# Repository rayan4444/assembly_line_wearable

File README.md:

# Crimson Dynamic

Hardware files and code for Crimson Dynamic (HAX Shenzhen 2019) sensor system prototyping

## Objective
Design a sensor system that adds value to the exoskeleton, specifically for use in an overhead assembly line in car factories. Potential insights the sensor system could provide:
* Task compliance: ensure a worker did not forget a bolt/nut on a car
* long term vibration exposure
* long term arm fatigue
* long term noise exposure
 * etc.

## REV 1
Sensor breakout to count the number of overhead drilling actions accomplished. Looked into doing an FFT analysis on IMU data and microphone data. Decided to settle on matching IMU data peaks to microphone data peaks. The same two sensors could be use to quantify the long term exposure to vibration, noise and fatigue.

## REV2
Pi HAT with sensors and UI to count the number of overhead drilling actions accomplished. A more efficient rendition of REV1 that is usable for demonstration.
> Note: Data is post processed and results are not given in real time

## REV3
NRF52 based sensor node with only IMU to monitor limb motion and vibration

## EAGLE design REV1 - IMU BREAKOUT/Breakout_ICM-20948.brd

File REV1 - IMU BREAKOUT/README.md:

Crimson Dynamics REV1

## Decription
Tries to detect drilling acitons by matching accelerometer peaks to microphone peaks. 
- Attempted doing it purely by placing the IMU on the hand holding the drill and running FFT but as the body acted as a low pass filter and filetered out higher frequencies that could have had information to characterise drilling vibrations. 
- Decided to addd a microphone to provide a second input. 
- In the final iteration of REV1, a simple peak finding algorithm from signal.scipy library is used to identify peaks in accelration and microphone recording. If the peaks happen within a second from each other they are assumed to belong to the same drilling action. Assuming the worker only does drilling tasks, this can be used to count the number of tasks. 

#### Notes:
- detailed assumptions in code
- sigle movements (vs vibrations) are not counted as drilling motion reducing false positives. 
- the code is in different scripts and run very slowly. 

## Hardware files 
ICM20948 breakout board slightly modified from the [Sparkfun one](https://www.sparkfun.com/products/15335)
## Python scripts 
#### Crimson_data_log.py
Records 10s of IMU and Microphone data, saves it in files "sensor_log.csv" and "output.wav" respectively. Later splits sensor log in "ax.csv", "ay.csv" and "az.csv" for further analysis. 

#### Crimson_action_count.py
- Opens data files and runs peak finding algorithm 
- Plots peaks found 
- For each of ax, ay, az and mic data, groups peaks that are within 0.5 seconds of each other as belonging to one "action" 
- To reduce the occurrance of false positives, only considers "actions" with peaks in at least two of the 3 accelerometer axes. 
- Only Counts "actions" with peaks in both microphone and accelerometer data (peak cluster averages within 1s of each other) 
- Prints total numberof valid "actions"

## OLD CODE
All the other python scripts used to test various things, such as IMU and microphone recording, data hadnling and plotting, FFT analysis etc. 

## TEST DATA
Data recorded with the prototype and used to tweak the peak finidng algorithm. TEST 5 is the best. 
In this version:
- 1 x ICM20948 9-Dof IMU (Eagle files for the breakout board are in this folder) 
- 1 x SPH0645LM4H MEMS Microphone breakout (from taobao)
- 1x Raspberry Pi (Raspberry Pi Zero W v1.1 used in my tests)

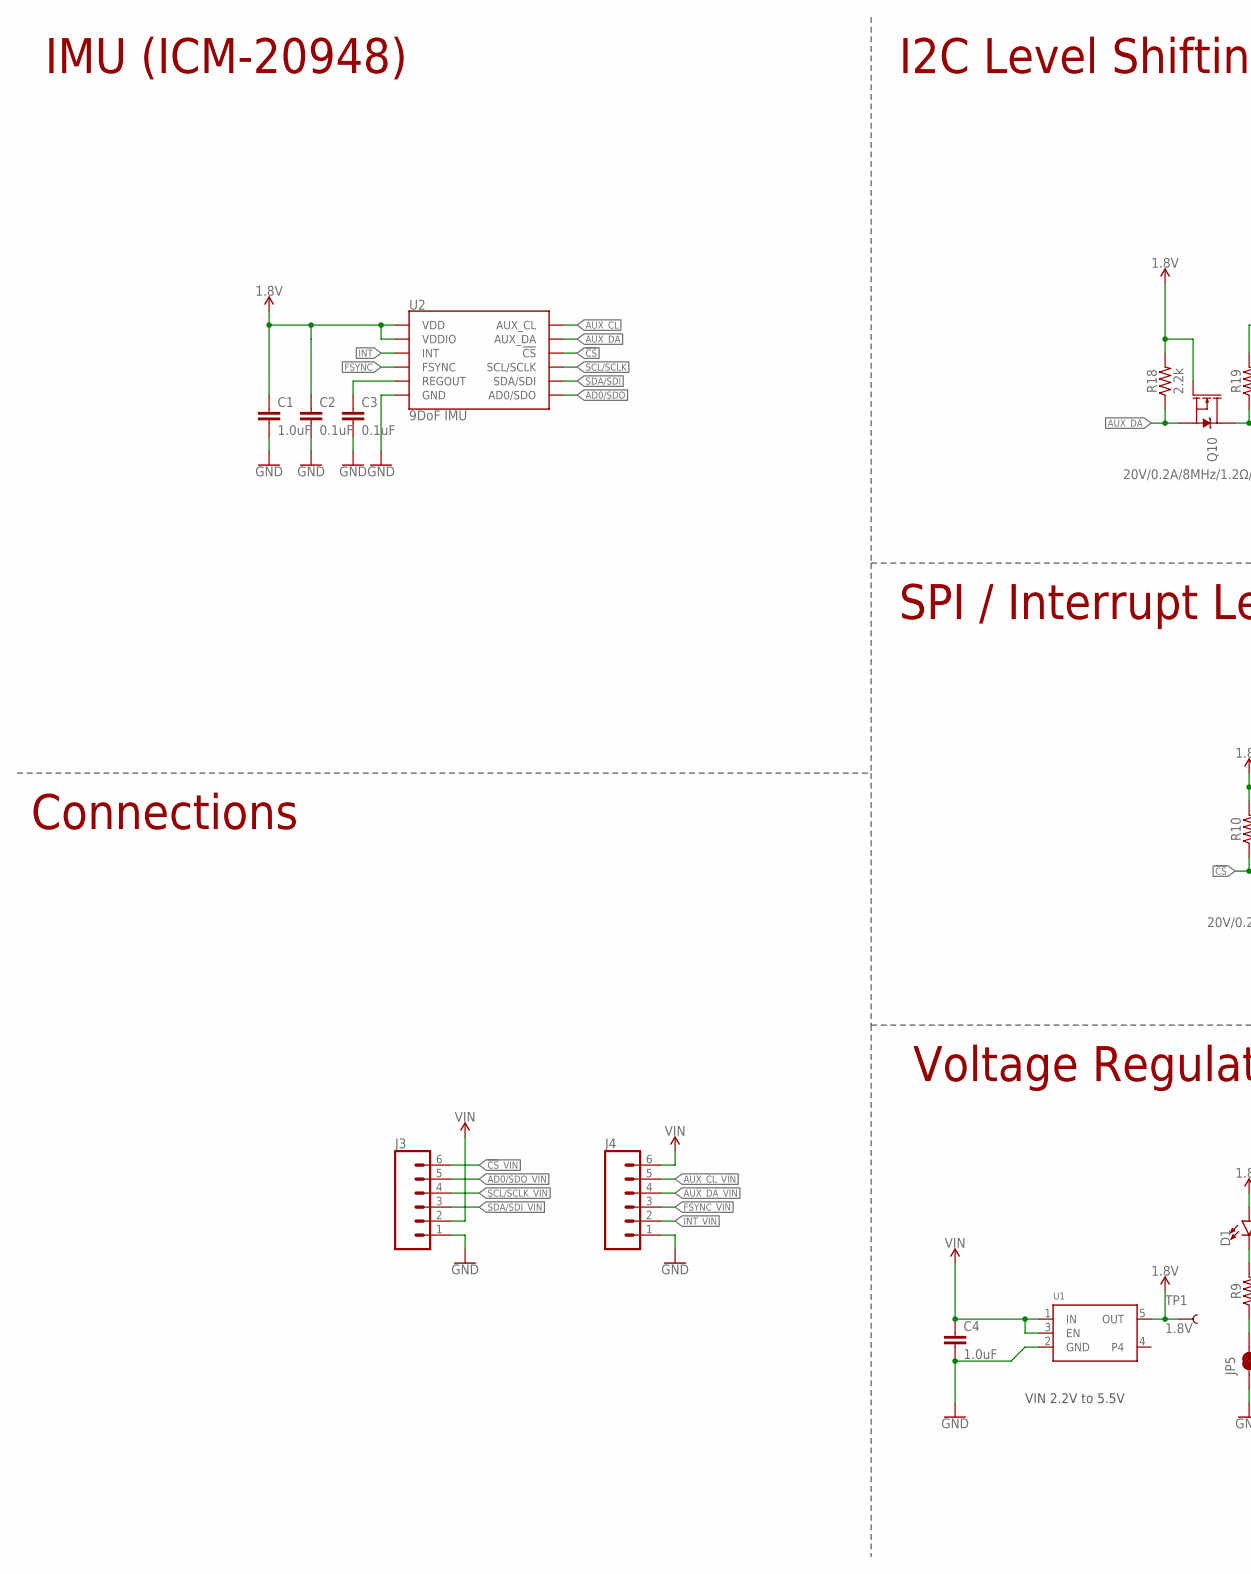
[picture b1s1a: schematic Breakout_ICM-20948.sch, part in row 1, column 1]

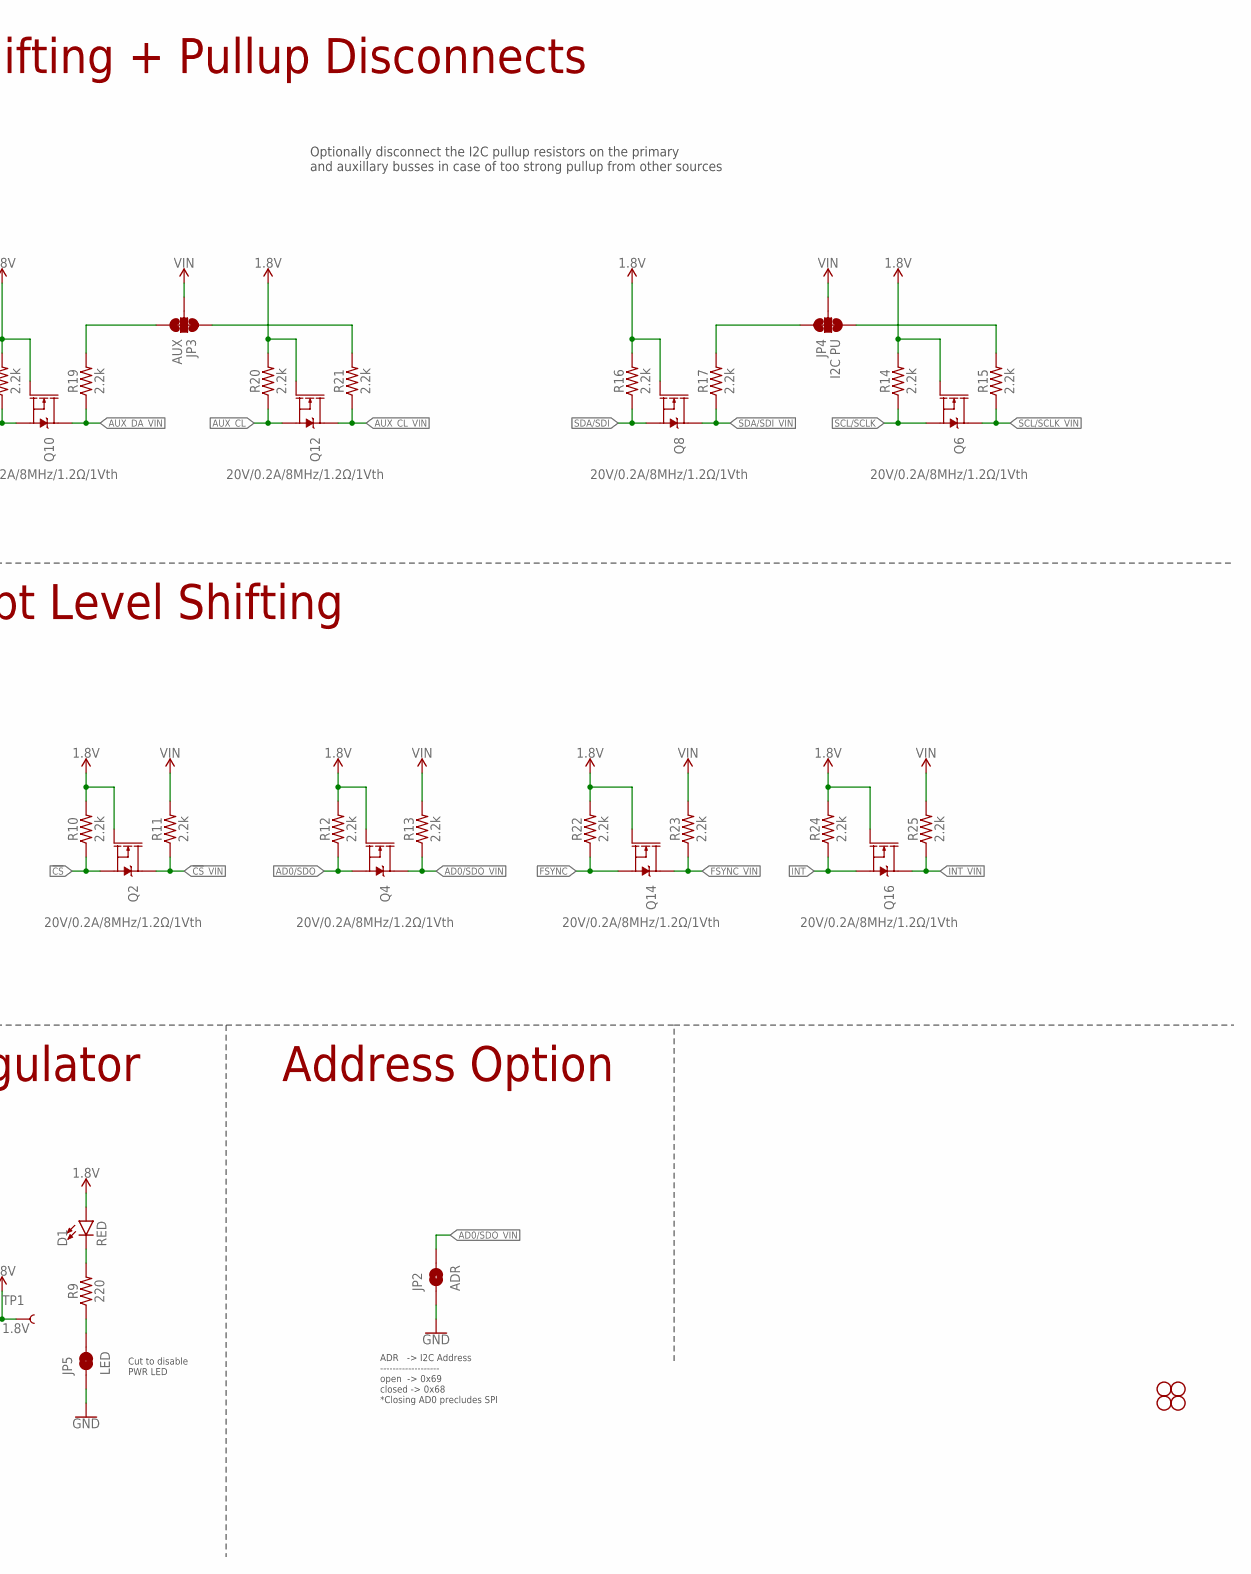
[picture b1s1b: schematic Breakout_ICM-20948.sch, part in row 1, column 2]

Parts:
C1, C4: 1.0uF; 0603
C2, C3: 0.1uF; 0603
D1: RED; LED-0603
H1, H2, H3, H4: STAND-OFF
J3, J4: CONN_06NO_SILK_NO_POP; 1X06_NO_SILK
JP2: ADR; SMT-JUMPER_2_NO_SILK
JP3: AUX; SMT-JUMPER_3_2-NC_TRACE_SILK
JP4: I2C PU; SMT-JUMPER_3_2-NC_TRACE_SILK
JP5: LED; SMT-JUMPER_2_NC_TRACE_SILK
Q2, Q4, Q6, Q8, Q10, Q12, Q14, Q16: 20V/0.2A/8MHz/1.2Ω/1Vth; SOT-416FL
R9: 220; 0603
R10, R11, R12, R13, R14, R15, R16, R17, R18, R19, R20, R21, R22, R23, R24, R25: 2.2k; 0402-TIGHT
TP1: 1.8V; PAD.03X.03
U1: MICROBUILDER_VREG_SOT23-5; MICROBUILDER_SOT23-5
U2: 9DoF IMU; QFN24-3X3

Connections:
1.8V: C1.1, C2.1, D1.A, Q2.1 (G), Q4.1 (G), Q6.1 (G), Q8.1 (G), Q10.1 (G), Q12.1 (G), Q14.1 (G), Q16.1 (G), R10.2, R12.2, R14.2, R16.2, R18.2, R20.2, R22.2, R24.2, TP1.P$1, U1.5 (OUT), U2.8 (VDDIO), U2.13 (VDD)
!CS: Q2.2 (S), R10.1, U2.22 (!CS)
!CS!_VIN: J3.6, Q2.3 (D), R11.1
AD0/SDO: Q4.2 (S), R12.1, U2.9 (AD0/SDO)
AD0/SDO_VIN: J3.5, JP2.2, Q4.3 (D), R13.1
AUX_CL: Q12.2 (S), R20.1, U2.7 (AUX_CL)
AUX_CL_VIN: J4.5, Q12.3 (D), R21.1
AUX_DA: Q10.2 (S), R18.1, U2.21 (AUX_DA)
AUX_DA_VIN: J4.4, Q10.3 (D), R19.1
FSYNC: Q14.2 (S), R22.1, U2.11 (FSYNC)
FSYNC_VIN: J4.3, Q14.3 (D), R23.1
GND: C1.2, C2.2, C3.2, C4.2, J3.1, J4.1, JP2.1, JP5.1, U1.2 (GND), U2.18 (GND), U2.20 (GND)
INT: Q16.2 (S), R24.1, U2.12 (INT)
INT_VIN: J4.2, Q16.3 (D), R25.1
unnamed: C3.1, U2.10 (REGOUT)
unnamed: JP4.3, R15.2
unnamed: JP4.1, R17.2
unnamed: JP3.1, R21.2
unnamed: JP3.3, R19.2
unnamed: D1.C, R9.2
unnamed: JP5.2, R9.1
SCL/SCLK: Q6.2 (S), R14.1, U2.23 (SCL/SCLK)
SCL/SCLK_VIN: J3.4, Q6.3 (D), R15.1
SDA/SDI: Q8.2 (S), R16.1, U2.24 (SDA/SDI)
SDA/SDI_VIN: J3.3, Q8.3 (D), R17.1
VIN: C4.1, J3.2, J4.6, JP3.2, JP4.2, R11.2, R13.2, R23.2, R25.2, U1.1 (IN), U1.3 (EN)

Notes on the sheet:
VIN 2.2V to 5.5V
IMU (ICM-20948)
I2C Level Shifting + Pullup Disconnects
Connections
Voltage Regulator
SPI / Interrupt Level Shifting
ADR -> I2C Address ------------------- open -> 0x69 closed -> 0x68 *Closing AD0 precludes SPI
Optionally disconnect the I2C pullup resistors on the primary and auxillary busses in case of too strong pullup from other sources
Cut to disable PWR LED
Address Option

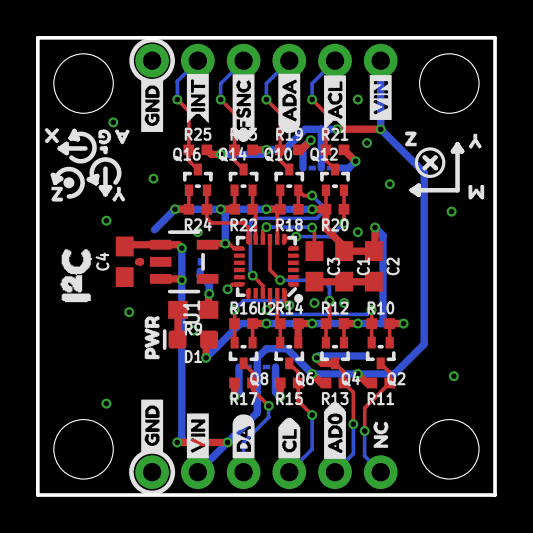
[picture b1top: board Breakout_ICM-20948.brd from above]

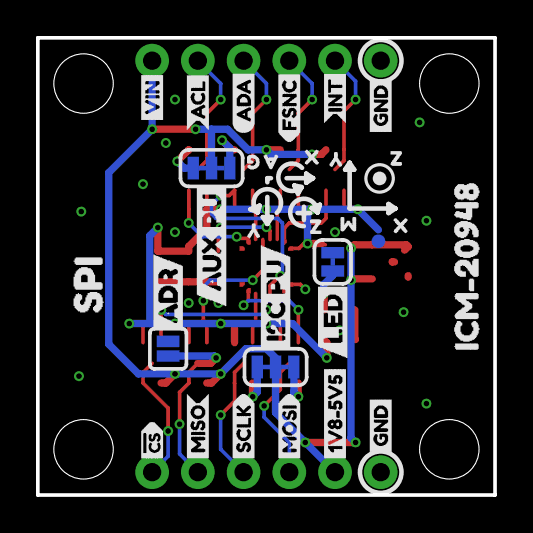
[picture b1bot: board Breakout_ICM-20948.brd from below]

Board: 2 copper layers, 25.4 x 25.4 mm, 92 parts (32 on the bottom side), 26 nets.

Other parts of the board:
U$1, U$2, U$22, U$24: GND4
U$3: PWR0
U$4, U$21: INT3
U$5, U$20: FSNC2
U$6, U$19: ACL1
U$7, U$18: ADA0
U$8: MISO13
U$9: MOSI14
U$10: SCLK15
U$11: #CS16
U$12: 1V8#5V57
U$13, U$30, U$44: VIN5
U$14: NC17
U$15: CL4
U$16: DA2
U$17: AD012
U$23: ADR2
U$25: I2C_PU21
U$26: SPI19
U$27: AUX_PU24
U$29: LED23
U$31: ICM#2094820
U$34, U$50, U$57: X0
U$35, U$41, U$51, U$58: Y1
U$36, U$42, U$52, U$59: Z2
U$37, U$60: G5
U$38, U$61: A4
U$39, U$49: M3
U$45: I#C1

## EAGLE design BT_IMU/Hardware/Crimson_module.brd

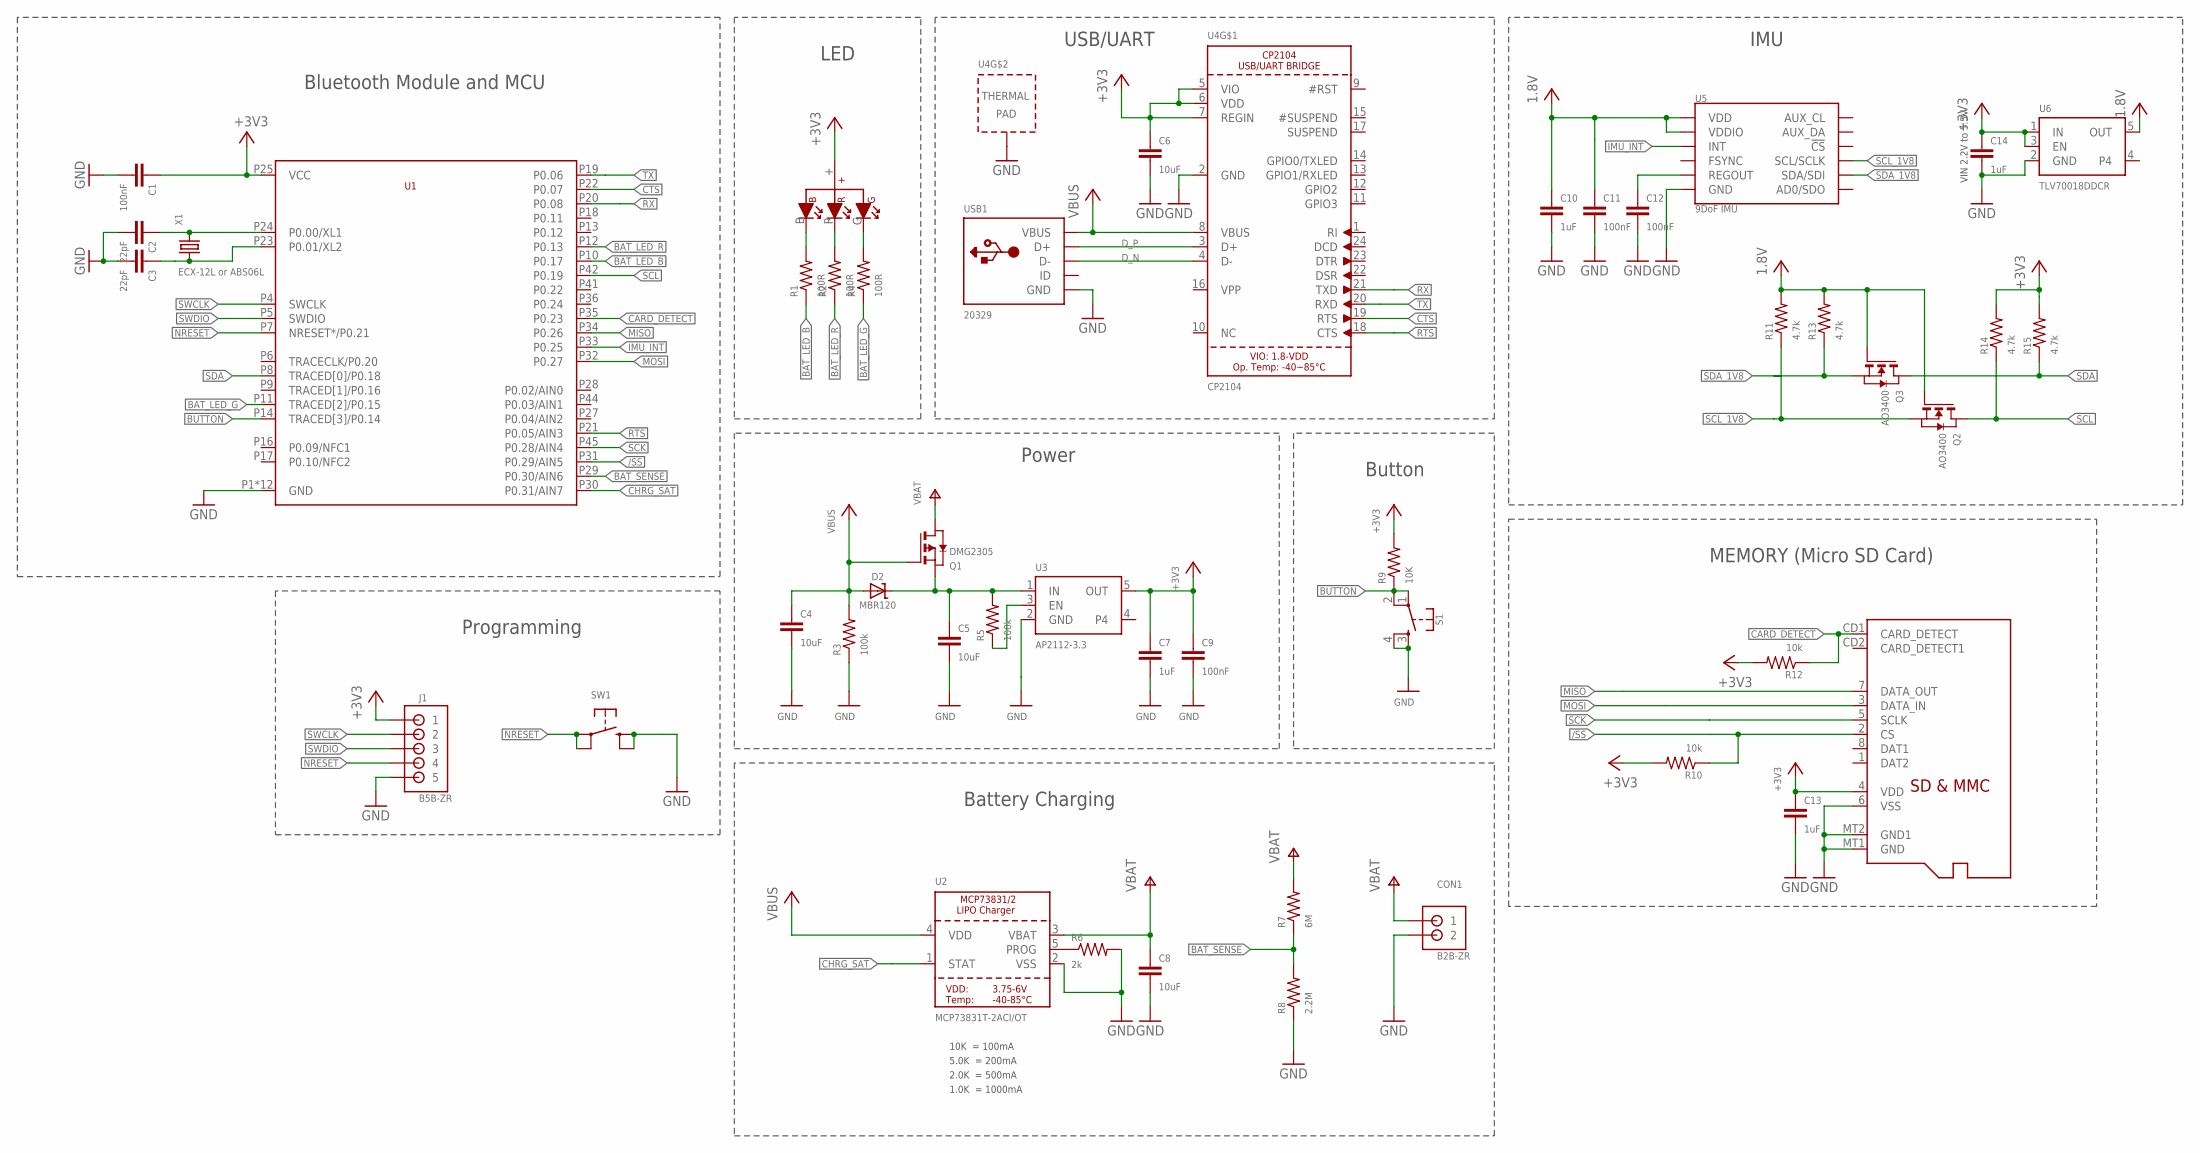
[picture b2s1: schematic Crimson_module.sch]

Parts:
C1, C9, C11, C12: 100nF; C0402
C2, C3: 22pF; C0402
C4, C5, C6, C8: 10uF; C0402
C7, C10, C13, C14: 1uF; C0402
CON1: B2B-ZR
D1: B2020RGBA
D2: MBR120; SOD-123
J1: B5B-ZR
Q1: DMG2305; SOT-23
Q2, Q3: AO3400; SOT-23
R1, R2, R4: 100R; R0402
R3, R5: 100k; R0402
R6: 2k; R0402
R7: 6M; R0402
R8: 2.2M; R0402
R9: 10K; R0402
R10, R12: 10k; R0402
R11, R13, R14, R15: 4.7k; R0402
S1: MOMENTARY-SWITCH-SPST-2-SMD-5.2MM; TACTILE_SWITCH_SMD_5.2MM
SD1: MICROSD
SW1: MICROBUILDER_SWITCH_TACT_SMT4.6X2.8; MICROBUILDER_BTN_KMR2_4.6X2.8
U1: BMD-350
U2: MCP73831T-2ACI/OT; SOT23-5
U3: AP2112-3.3; SOT23-5
U4: CP2104; QFN24_4MM_SMSC
U5: 9DoF IMU; QFN24-3X3
U6: TLV70018DDCR; MICROBUILDER_SOT23-5
USB1: 20329; 4UCONN_20329_V2
X1: ECX-12L or ABS06L; 2.0X1.2

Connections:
+3V3: C1.1, C6.1, C7.1, C9.1, C13.1, C14.1, D1.+, J1.1, R9.2, R10.2, R12.2, R14.2, R15.2, SD1.4 (VDD), U1.P25 (VCC), U3.5 (OUT), U4.5 (VIO), U4.6 (VDD), U4.7 (REGIN), U6.1 (IN), U6.3 (EN)
+5V: C4.1, D2.A, Q1.G, R3.2, U2.4 (VDD), U4.8 (VBUS), USB1.VBUS
/SS: R10.1, SD1.2 (CS), U1.P31 (P0.29/AIN5)
BAT_LED_B: R1.1, U1.P10 (P0.17)
BAT_LED_G: R4.1, U1.P11 (TRACED[2]/P0.15)
BAT_LED_R: R2.1, U1.P12 (P0.13)
BAT_SENSE: R7.1, R8.2, U1.P29 (P0.30/AIN6)
BUTTON: R9.1, S1.1, S1.2, U1.P14 (TRACED[3]/P0.14)
CARD_DETECT: R12.1, SD1.CD1 (CARD_DETECT), U1.P35 (P0.23)
CHRG_SAT: U1.P30 (P0.31/AIN7), U2.1 (STAT)
CTS: U1.P22 (P0.07), U4.19 (RTS)
D_N: U4.4 (D-), USB1.D-
D_P: U4.3 (D+), USB1.D+
EN: R5.1, U3.3 (EN)
GND: C1.2, C2.2, C3.2, C4.2, C5.2, C6.2, C7.2, C8.2, C9.2, C10.2, C11.2, C12.2, C13.2, C14.2, CON1.2, J1.5, R3.1, R6.2, R8.1, S1.3, S1.4, SD1.6 (VSS), SD1.MT1 (GND), SD1.MT2 (GND1), SW1.B (S), SW1.B' (S1), U1.P1 (GND), U1.P2 (GND), U1.P3 (GND), U1.P15 (GND), U1.P26 (GND), U1.P37 (GND), U1.P38 (GND), U1.P39 (GND), U1.P40 (GND), U1.P43 (GND), U1.P46 (GND), U1.P47 (GND), U2.2 (VSS), U3.2 (GND), U4.2 (GND), U4.THERM (TP), U5.18 (GND), U5.20 (GND), U6.2 (GND), USB1.BASE@1 (GND), USB1.BASE@2 (GND), USB1.GND, USB1.SPRT@1 (GND), USB1.SPRT@2 (GND), USB1.SPRT@3 (GND), USB1.SPRT@4 (GND)
IMU_INT: U1.P33 (P0.25), U5.12 (INT)
MISO: SD1.7 (DATA_OUT), U1.P34 (P0.26)
MOSI: SD1.3 (DATA_IN), U1.P32 (P0.27)
unnamed: R6.1, U2.5 (PROG)
unnamed: C12.1, U5.10 (REGOUT)
unnamed: C3.1, U1.P23 (P0.01/XL2), X1.1
unnamed: D1.B, R1.2
unnamed: D1.R, R2.2
unnamed: D1.G, R4.2
unnamed: C2.1, U1.P24 (P0.00/XL1), X1.2
unnamed: C5.1, D2.C, Q1.S, R5.2, U3.1 (IN)
NRESET: J1.4, SW1.A, SW1.A' (P1), U1.P7 (NRESET*/P0.21)
RTS: U1.P21 (P0.05/AIN3), U4.18 (CTS)
RX: U1.P20 (P0.08), U4.21 (TXD)
SCK: SD1.5 (SCLK), U1.P45 (P0.28/AIN4)
SCL: Q2.D, R14.1, U1.P42 (P0.19)
SCL_1V8: Q2.S, R11.1, U5.23 (SCL/SCLK)
SDA: Q3.D, R15.1, U1.P8 (TRACED[0]/P0.18)
SDA_1V8: Q3.S, R13.1, U5.24 (SDA/SDI)
SWCLK: J1.2, U1.P4 (SWCLK)
SWDIO: J1.3, U1.P5 (SWDIO)
TX: U1.P19 (P0.06), U4.20 (RXD)
V+: C8.1, CON1.1, Q1.D, R7.2, U2.3 (VBAT)
VCC: C10.1, C11.1, Q2.G, Q3.G, R11.2, R13.2, U5.8 (VDDIO), U5.13 (VDD), U6.5 (OUT)

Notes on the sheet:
10K = 100mA
5.0K = 200mA
2.0K = 500mA
1.0K = 1000mA
Battery Charging
Bluetooth Module and MCU
LED
USB/UART
Power
Button
MEMORY (Micro SD Card)
IMU
VIN 2.2V to 5.5V
Programming

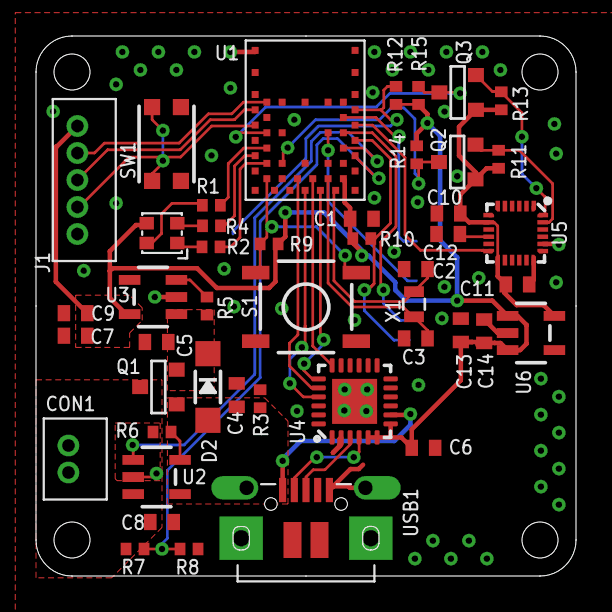
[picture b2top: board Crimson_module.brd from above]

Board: 2 copper layers, 30.0 x 30.0 mm, 47 parts (1 on the bottom side), 39 nets.

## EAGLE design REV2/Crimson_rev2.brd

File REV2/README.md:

Crimson Dynamics REV2

## Description
Pi HAT with sensors and UI to count the number of overhead drilling actions accomlished:
- 1 x ICM20948 9-Dof IMU 
- 1 x SPH0645LM4H MEMS Microphone
- 3 x pushbuttons
- 2 x LEDs
- 1 x 128x32 I2C OLED Display 
- 1 x Raspberry Pi Zero W v1.1

#### Python scripts
Crimson_button.py runs at boot and imports functions from Crimson_data_log.py and Crimson_action_count.py

#### Usage:
- Boot up the Rasberry Pi and wait for the OLED display to refresh. This might take up to 3-4 min.  
- Pressing "start" button records 40s of data from the microphone and the IMU (x,y,z acceleration to be specific). 
- Green LED lights up and stays on after the recording is done if everything went well 
- Pressing "stop" button analyses results, using the latest action counting technique from rev1.
> By default plotting is not enabled because it slows everything down and requires a way to close the plot window to proceed. but in case it is needed, plt.show() can be uncommented from Crimson_action_count.py
- Orange LED lights up and stays on after processing is done if everything went well. The final count will show on the display for a couple seconds. 
- Pressing "BTN" button deletes all data records. If you want to keep the recorded data, ssh into the Rpi and copy it to another directory before deleting it. 
> If you don't delete the data, the next recording will just be appended to the current file and give false action count results. 

#### Notes: 
- Display breakout on the PCB doesn't match the module we purchsed so some reworking had to be done to be able to wire it properly 
- A single python script that can be run from boot. It imports functions from two other python files. These functions are very similar to the REV1 code, a little has been done to optimise it. 
- To view code outputs you can hook up a display to the pi or ssh into it (or use VNC). You can also uncomment print statements in the code to track the action countinfg process. 
- [Tutorial to change microphone sensitivity](https://learn.adafruit.com/adafruit-i2s-mems-microphone-breakout/raspberry-pi-wiring-and-test)

## Hardware files
Eagle files and gerber files for the Pi HAT

## Other files
* Notes from meeting with Bunnie on 24.09.2019, discussing how to go about improving the current demo and going about the next version

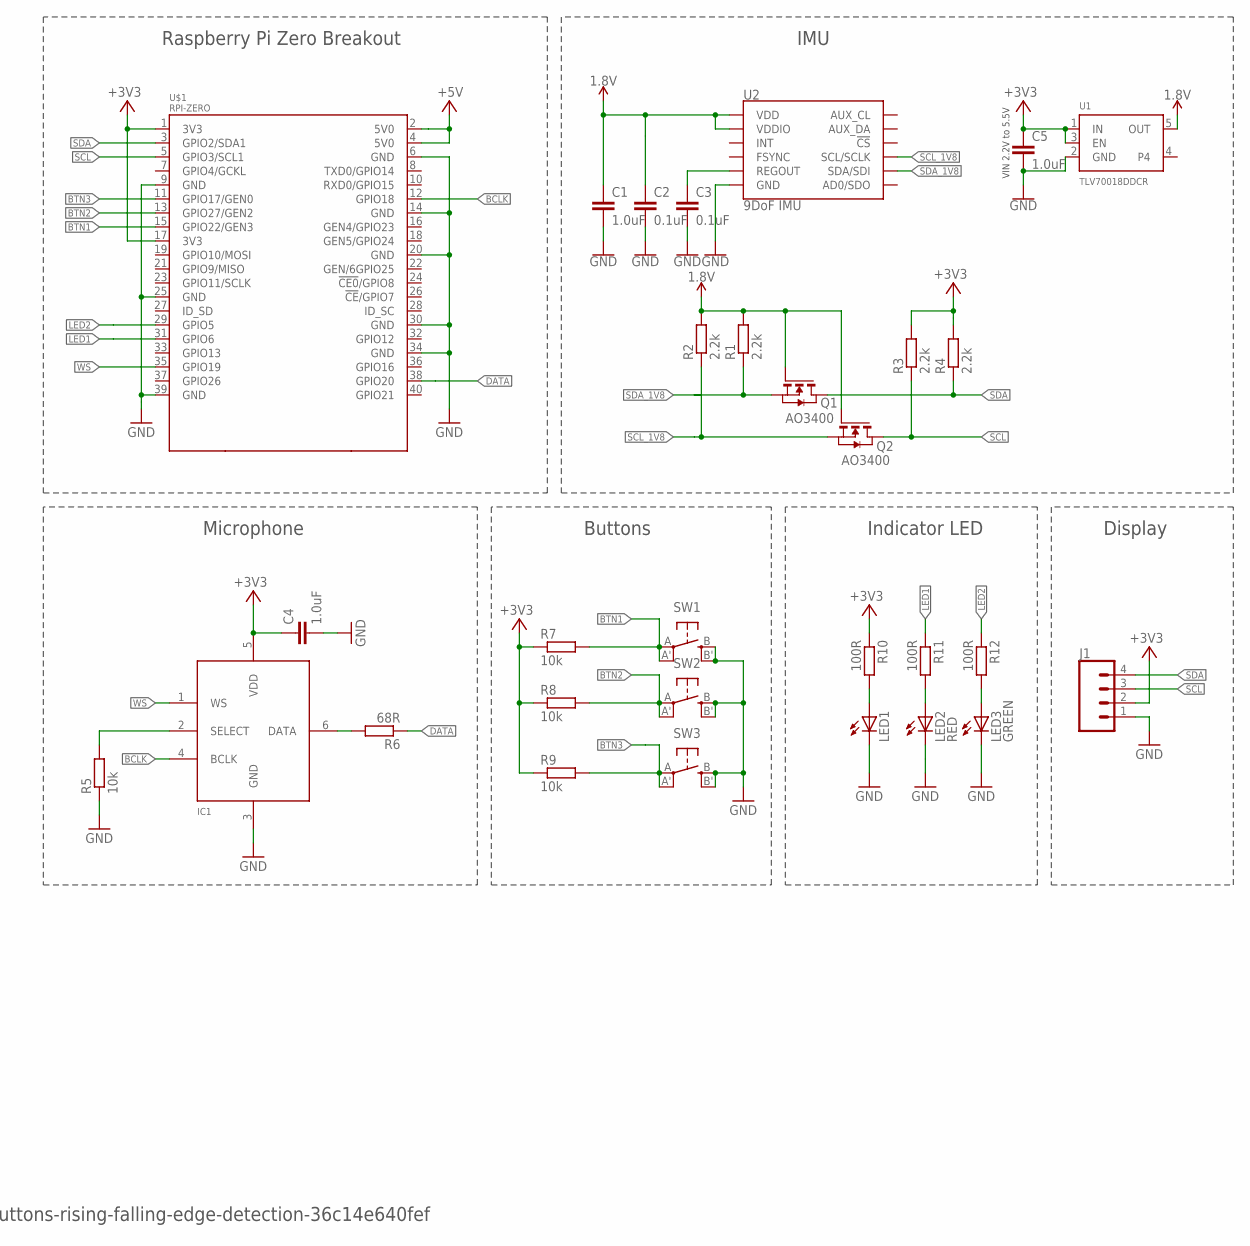
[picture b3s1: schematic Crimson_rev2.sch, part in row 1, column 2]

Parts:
C1, C4, C5: 1.0uF; 0402
C2, C3: 0.1uF; 0402
IC1: MIC_I2S_SPH0645; SPH0645LM4H
J1: CONN_04; 1X04
LED1: LEDCHIPLED_0603; CHIPLED_0603
LED2: RED; CHIPLED_0603
LED3: GREEN; CHIPLED_0603
Q1, Q2: AO3400; SOT-23
R1, R2, R3, R4: 2.2k; R0402
R5, R7, R8, R9: 10k; R0402
R6: 68R; R0402
R10, R11, R12: 100R; R0402
SW1, SW2, SW3: SPST_TACT-EVQQ2; EVQ-Q2
U1: TLV70018DDCR; MICROBUILDER_SOT23-5
U2: 9DoF IMU; QFN24-3X3
U$1: RPI-ZERO; RASPBERRYPI_BASTELSTUBE_V13_RASPI_BOARD_B+_FULL

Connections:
1.8V: C1.1, C2.1, Q1.G, Q2.G, R1.2, R2.2, U1.5 (OUT), U2.8 (VDDIO), U2.13 (VDD)
+3V3: C4.1, C5.1, IC1.5 (VDD), J1.2, R3.2, R4.2, R7.2, R8.2, R9.2, R10.1, U1.1 (IN), U1.3 (EN), U$1.1 (3V3), U$1.17 (3V3)
+5V: U$1.2 (5V0), U$1.4 (5V0)
BCLK: IC1.4 (BCLK), U$1.12 (GPIO18)
BTN1: R7.1, SW1.A, SW1.A' (P1), U$1.15 (GPIO22/GEN3)
BTN2: R8.1, SW2.A, SW2.A' (P1), U$1.13 (GPIO27/GEN2)
BTN3: R9.1, SW3.A, SW3.A' (P1), U$1.11 (GPIO17/GEN0)
DATA: R6.1, U$1.38 (GPIO20)
GND: C1.2, C2.2, C3.2, C4.2, C5.2, IC1.3 (GND), J1.1, LED1.C, LED2.C, LED3.C, R5.1, SW1.B (S), SW1.B' (S1), SW2.B (S), SW2.B' (S1), SW3.B (S), SW3.B' (S1), U1.2 (GND), U2.18 (GND), U2.20 (GND), U$1.6 (GND), U$1.9 (GND), U$1.14 (GND), U$1.20 (GND), U$1.25 (GND), U$1.30 (GND), U$1.34 (GND), U$1.39 (GND)
LED1: R11.1, U$1.31 (GPIO6)
LED2: R12.1, U$1.29 (GPIO5)
unnamed: C3.1, U2.10 (REGOUT)
unnamed: IC1.2 (SELECT), R5.2
unnamed: IC1.6 (DATA), R6.2
unnamed: LED1.A, R10.2
unnamed: LED2.A, R11.2
unnamed: LED3.A, R12.2
SCL: J1.3, Q2.D, R3.1, U$1.5 (GPIO3/SCL1)
SCL_1V8: Q2.S, R2.1, U2.23 (SCL/SCLK)
SDA: J1.4, Q1.D, R4.1, U$1.3 (GPIO2/SDA1)
SDA_1V8: Q1.S, R1.1, U2.24 (SDA/SDI)
WS: IC1.1 (WS), U$1.35 (GPIO19)

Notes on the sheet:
IMU
Microphone
Buttons
Display
Indicator LED
Reference: https://medium.com/@rxseger/interrupt-driven-i-o-on-raspberry-pi-3-with-leds-and-pushbuttons-rising-falling-edge-detection-36c14e640fef
VIN 2.2V to 5.5V
Raspberry Pi Zero Breakout

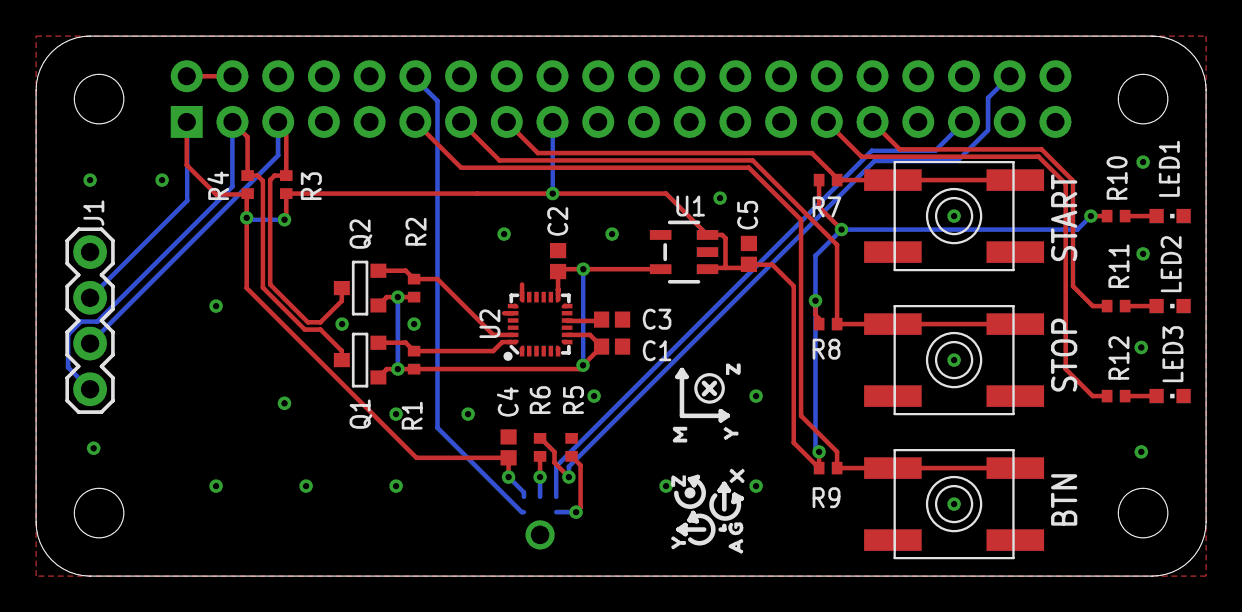
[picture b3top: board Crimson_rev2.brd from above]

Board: 2 copper layers, 65.0 x 30.0 mm, 38 parts (1 on the bottom side), 22 nets.

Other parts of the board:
U$34: X0
U$35, U$41: Y1
U$36, U$42: Z2
U$37: G5
U$38: A4
U$39: M3

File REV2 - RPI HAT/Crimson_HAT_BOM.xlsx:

# | Parts | Value | Qty | Package
1 | C2, C3 | 100nF | 2 | C0402 | https://item.szlcsc.com/287818.html
2 | C1, C4, C5 | 1uF | 3 | C0402 | https://item.szlcsc.com/53938.html
3 | R10, R11, R12 | 100R | 3 | R0402 | no need to buy
4 | R5, R7, R8, R9 | 10k | 4 | R0402 | https://item.szlcsc.com/26274.html
5 | R1, R2, R3, R4 | 2.2k | 4 | R0402 | no need to buy
6 | R6 | 68R | 1 | R0402 | https://item.szlcsc.com/101732.html
7 | U2 | ICM-20948 | 1 | QFN24-3X3 | https://detail.tmall.com/item.htm?id=597841363170
8 | Q1, Q2 | AO3400 | 2 | SOT-23 | https://item.szlcsc.com/192487.html
9 | LED3 | GREEN | 1 | CHIPLED_0603 | https://item.szlcsc.com/119599.html
11 | LED2 | RED | 1 | CHIPLED_0603 | https://item.szlcsc.com/193260.html
10 | IC1 | MIC_I2S_SPH0645 | 1 | SPH0645LM4H | https://item.taobao.com/item.htm?id=555562766149
13 | SW1, SW2, SW3 | SPST_TACT-EVQQ2 | 3 | EVQ-Q2 | no need to buy
14 | U1 | TLV70018DDCR | 1 | SOT23-5 | https://item.szlcsc.com/81068.html
 | SCREEN: |  |  |  | https://item.taobao.com/item.htm?id=558142276427

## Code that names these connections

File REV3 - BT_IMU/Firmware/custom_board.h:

#ifndef CRIMSON_BOARD_H
#define CRIMSON_BOARD_H

#ifdef __cplusplus
extern "C" {
#endif //CRIMSON_BOARD_H

#include "nrf_gpio.h"
#define LEDS_NUMBER    3

#define LED_R 13
#define LED_G 15
#define LED_B 17

#define LEDS_ACTIVE_STATE 1

#define LEDS_INV_MASK  LEDS_MASK

#define LEDS_LIST { LED_R, LED_G, LED_B}

#define BSP_LED_0      LED_B
#define BSP_LED_1      LED_G
#define BSP_LED_2      LED_R



#define BUTTONS_NUMBER 1
#define BUTTONS_ACTIVE_STATE 0 

#define BUTTON_1 14

#define BUTTONS_LIST { BUTTON_1 }

#define BSP_BUTTON_0   BUTTON_1


#define RX_PIN_NUMBER  8
#define TX_PIN_NUMBER  6
#define CTS_PIN_NUMBER 7
#define RTS_PIN_NUMBER 5
#define HWFC           true

// #define SPIM0_SCK_PIN   28  // SPI clock GPIO pin number.
// #define SPIM0_MOSI_PIN  27  // SPI Master Out Slave In GPIO pin number.
// #define SPIM0_MISO_PIN  26  // SPI Master In Slave Out GPIO pin number.
// #define SPIM0_SS_PIN    29  // SPI Slave Select GPIO pin number.

#define SDC_SCK_PIN     28 //SDC serial clock (SCK) pin.
#define SDC_MOSI_PIN    27 //SDC serial data in (DI) pin.
#define SDC_MISO_PIN    26 //SDC serial data out (DO) pin.
#define SDC_CS_PIN      29 //SDC chip select (CS) pin.

#define SCL_PIN 19
#define SDA_PIN 18

#define IMU_INT_PIN 25
#define CARD_DETECT_PIN 23
#define BAT_SENSE_PIN 30 //AIN6

//stuff the NRF examples use and I can remove later

#define BUTTON_PULL    NRF_GPIO_PIN_PULLUP
#ifdef __cplusplus
}
#endif

#endif // 

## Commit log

2019-07-26 Plotting single potentiometer data from Arduino
2019-07-26 three lines on one graph
2019-08-12 Switch to raspi Zero W, plots IMU all 9 axes
2019-08-12 renamed file
2019-08-13 Working code with basic FF on accelerometer data
2019-09-07 Working prototype of recording data, peak finding and action matching
2019-09-07 added test data
2019-09-10 changed test time to 40s
2019-09-18 Added rev2 Hardware files
2019-09-24 Madded meeting notes. minor code changes
2019-09-24 update gitignore
2019-09-24 changed scripts to functions, can run at boot
2019-09-24 updated documentation
2019-09-25 minor tweaks
2019-12-03 PCB files for IMU dev board
2020-01-27 timer, led, ble, i2c to sensor
2020-02-12 sensor up/dpwn stable
2020-02-18 saves events logs to sd card
2020-02-19 mod debug notes
2020-08-12 Post project commit

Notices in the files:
parts and their libraries:
microbuilder: This work is placed in the public domain, and may be freely used for commercial and non-commercial work with the following conditions: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
crystal-geyer_V1_0: Copyright: Geyer-Electronic
